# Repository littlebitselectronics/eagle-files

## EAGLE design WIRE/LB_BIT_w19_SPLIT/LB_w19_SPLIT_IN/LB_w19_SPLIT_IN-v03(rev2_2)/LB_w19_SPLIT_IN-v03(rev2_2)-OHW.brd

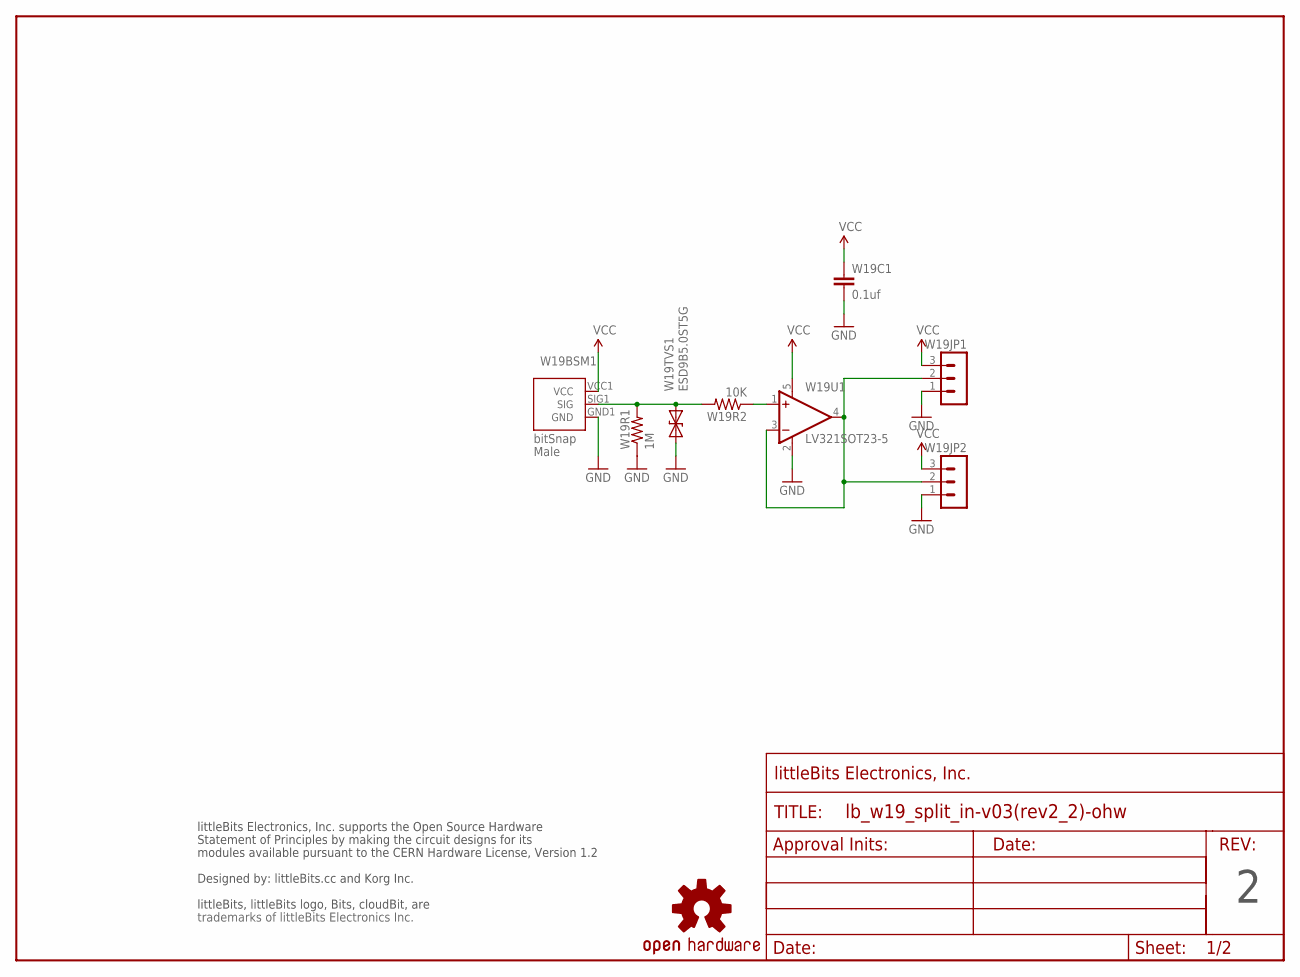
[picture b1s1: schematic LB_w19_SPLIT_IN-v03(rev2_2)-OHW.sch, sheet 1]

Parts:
FRAME1: FRAME-LETTER-OHWOHW; FABDWG01-OHW
U$3: OSHW-LOGOL; OSHW-LOGO-L
U$4: OSHWCREDIT-KORG
W19BSM1: BITSNAP_V03_MALE
W19C1: 0.1uf; CAP-0603
W19JP1, W19JP2: MA03-1SMD; 1X03-1MM-RA
W19R1: 1M; RES-0603
W19R2: 10K; RES-0603
W19TVS1: ESD9B5.0ST5G; SOD-923
W19U1: LV321SOT23-5; SOT23-5

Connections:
GND: W19BSM1.GND1 (GND), W19C1.2, W19JP1.1, W19JP2.1, W19R1.1, W19TVS1.1 (A), W19U1.2 (V-)
unnamed: W19BSM1.SIG1 (SIG), W19R1.2, W19R2.2, W19TVS1.2 (C)
unnamed: W19R2.1, W19U1.1 (+IN)
unnamed: W19JP1.2, W19JP2.2, W19U1.3 (-IN), W19U1.4 (OUT)
VCC: W19BSM1.VCC1 (VCC), W19C1.1, W19JP1.3, W19JP2.3, W19U1.5 (V+)

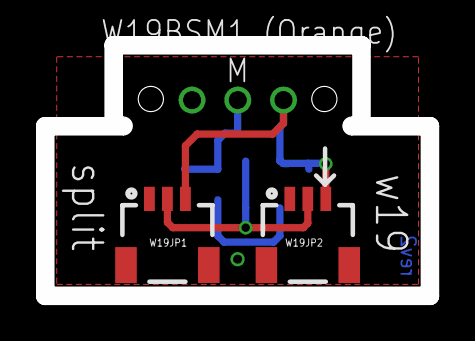
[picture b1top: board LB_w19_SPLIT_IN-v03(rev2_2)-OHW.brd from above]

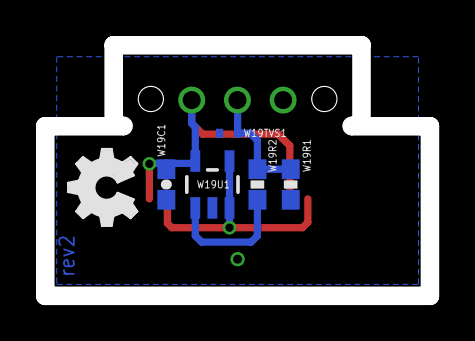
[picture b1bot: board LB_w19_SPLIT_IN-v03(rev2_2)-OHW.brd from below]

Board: 2 copper layers, 21.4 x 13.9 mm, 12 parts (5 on the bottom side), 5 nets.

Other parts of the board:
U$2: OSHW_FILLX150_NOTEXT

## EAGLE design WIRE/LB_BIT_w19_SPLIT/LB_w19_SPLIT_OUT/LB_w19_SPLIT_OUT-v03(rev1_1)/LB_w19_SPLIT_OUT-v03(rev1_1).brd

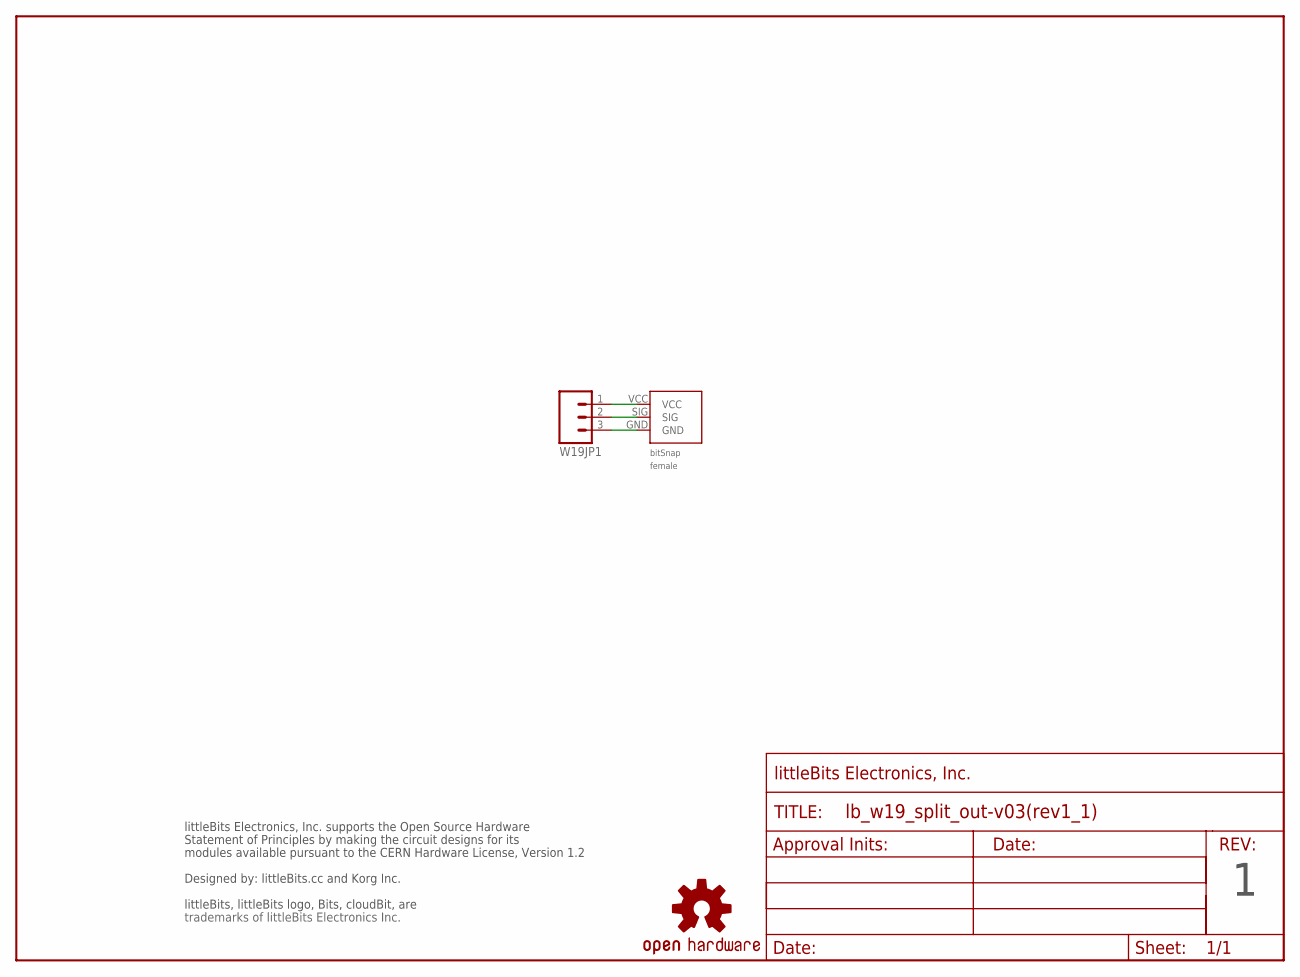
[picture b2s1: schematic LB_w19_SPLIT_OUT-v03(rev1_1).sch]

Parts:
FRAME1: FRAME-LETTER-OHWOHW; FABDWG01-OHW
U$3: OSHW-LOGOL; OSHW-LOGO-L
U$4: OSHWCREDIT-KORG
W19BSF1: BITSNAP_V03_FEMALE
W19JP1: M03SMD; 1X03-1MM-RA

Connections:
GND: W19BSF1.GND, W19JP1.3
SIG: W19BSF1.SIG, W19JP1.2
VCC: W19BSF1.VCC, W19JP1.1

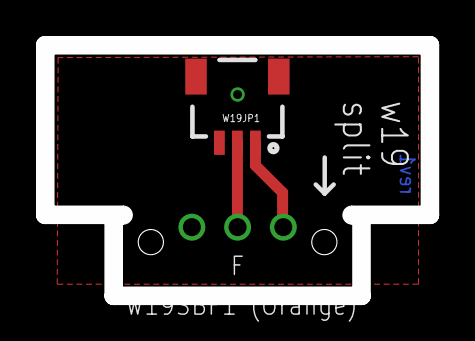
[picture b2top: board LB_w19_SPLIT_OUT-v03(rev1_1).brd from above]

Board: 2 copper layers, 21.4 x 13.9 mm, 6 parts (0 on the bottom side), 3 nets.

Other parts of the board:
U$2: OSHW_FILLX150_NOTEXT

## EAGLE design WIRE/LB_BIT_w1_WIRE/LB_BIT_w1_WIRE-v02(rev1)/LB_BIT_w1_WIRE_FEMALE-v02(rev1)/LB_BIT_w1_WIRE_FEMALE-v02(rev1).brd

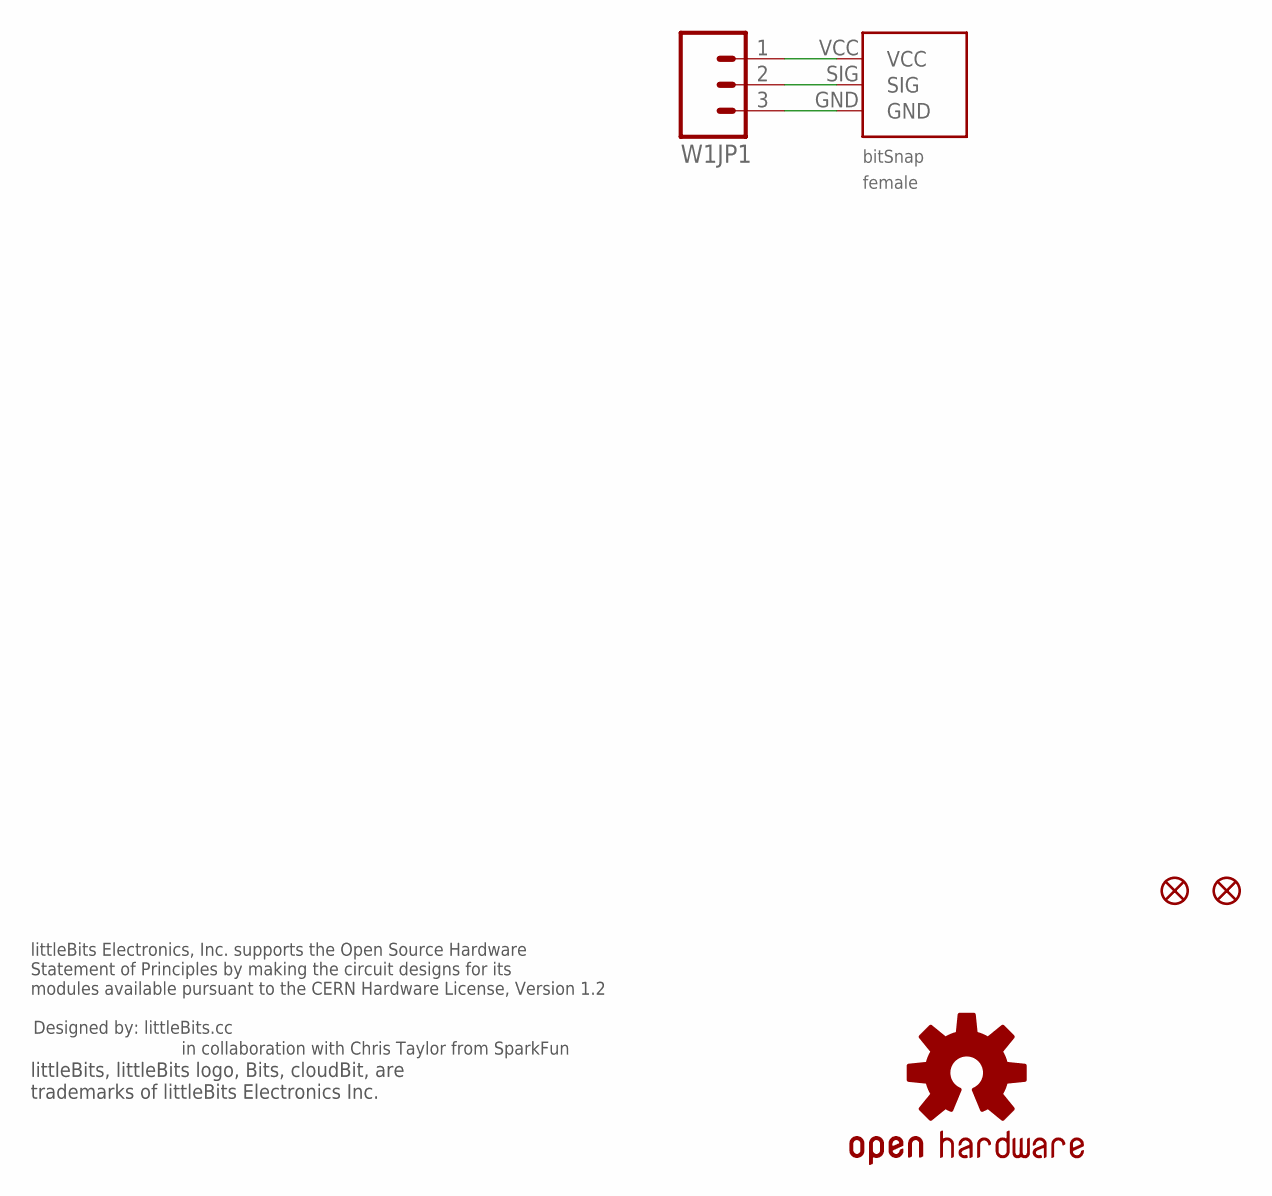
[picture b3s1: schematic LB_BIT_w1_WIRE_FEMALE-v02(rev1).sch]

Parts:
JP2, JP3: FIDUCIAL1X2.5; FIDUCIAL-1X2.5
U$1: LB_CREDITS; OSHWCREDIT
U$3: OSHW-LOGOL; OSHW-LOGO-L
W1BSF: BITSNAP_FEMALE
W1JP1: M03SMD; 1X03-1MM-RA

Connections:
GND: W1BSF.GND, W1JP1.3
SIG: W1BSF.SIG, W1JP1.2
VCC: W1BSF.VCC, W1JP1.1

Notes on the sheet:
in collaboration with Chris Taylor from SparkFun

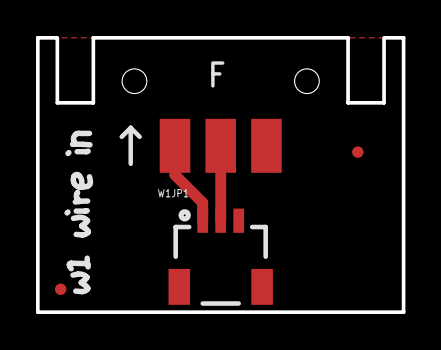
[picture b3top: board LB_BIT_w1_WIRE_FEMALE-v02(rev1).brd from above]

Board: 2 copper layers, 20.3 x 15.2 mm, 7 parts (0 on the bottom side), 3 nets.

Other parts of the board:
U$2: OSHW_FILLX150_NOTEXT

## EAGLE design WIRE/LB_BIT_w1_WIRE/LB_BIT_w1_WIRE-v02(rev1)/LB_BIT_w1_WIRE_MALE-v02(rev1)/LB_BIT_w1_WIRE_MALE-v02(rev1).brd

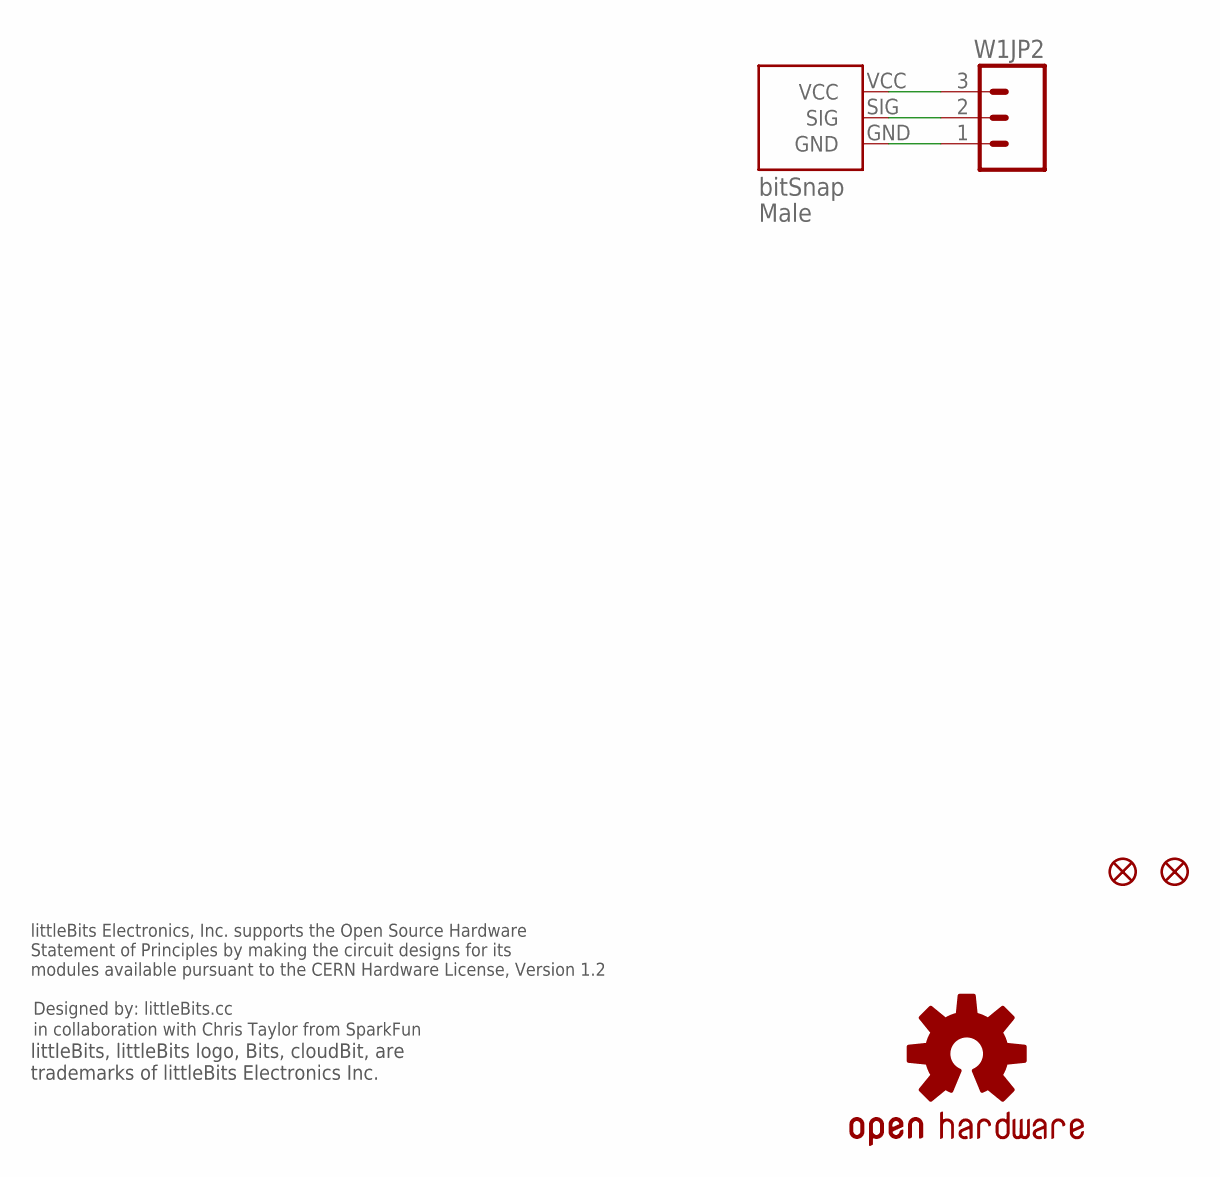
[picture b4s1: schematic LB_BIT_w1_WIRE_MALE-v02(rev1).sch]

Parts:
JP1, JP2: FIDUCIAL1X2.5; FIDUCIAL-1X2.5
U$1: OSHWCREDIT
U$3: OSHW-LOGOL; OSHW-LOGO-L
W1BSM: BITSNAP_MALE
W1JP2: M03SMD; 1X03-1MM-RA

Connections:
GND: W1BSM.GND, W1JP2.1
SIG: W1BSM.SIG, W1JP2.2
VCC: W1BSM.VCC, W1JP2.3

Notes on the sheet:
in collaboration with Chris Taylor from SparkFun

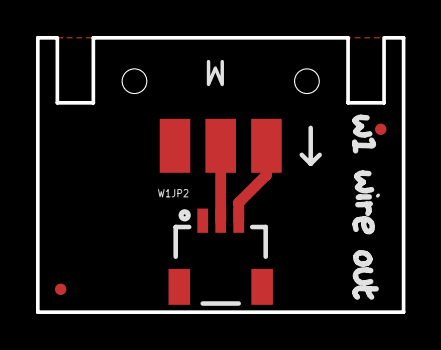
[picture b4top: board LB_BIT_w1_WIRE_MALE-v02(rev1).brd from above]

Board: 2 copper layers, 20.3 x 15.2 mm, 7 parts (0 on the bottom side), 3 nets.

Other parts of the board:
U$4: OSHW_FILLX150_NOTEXT

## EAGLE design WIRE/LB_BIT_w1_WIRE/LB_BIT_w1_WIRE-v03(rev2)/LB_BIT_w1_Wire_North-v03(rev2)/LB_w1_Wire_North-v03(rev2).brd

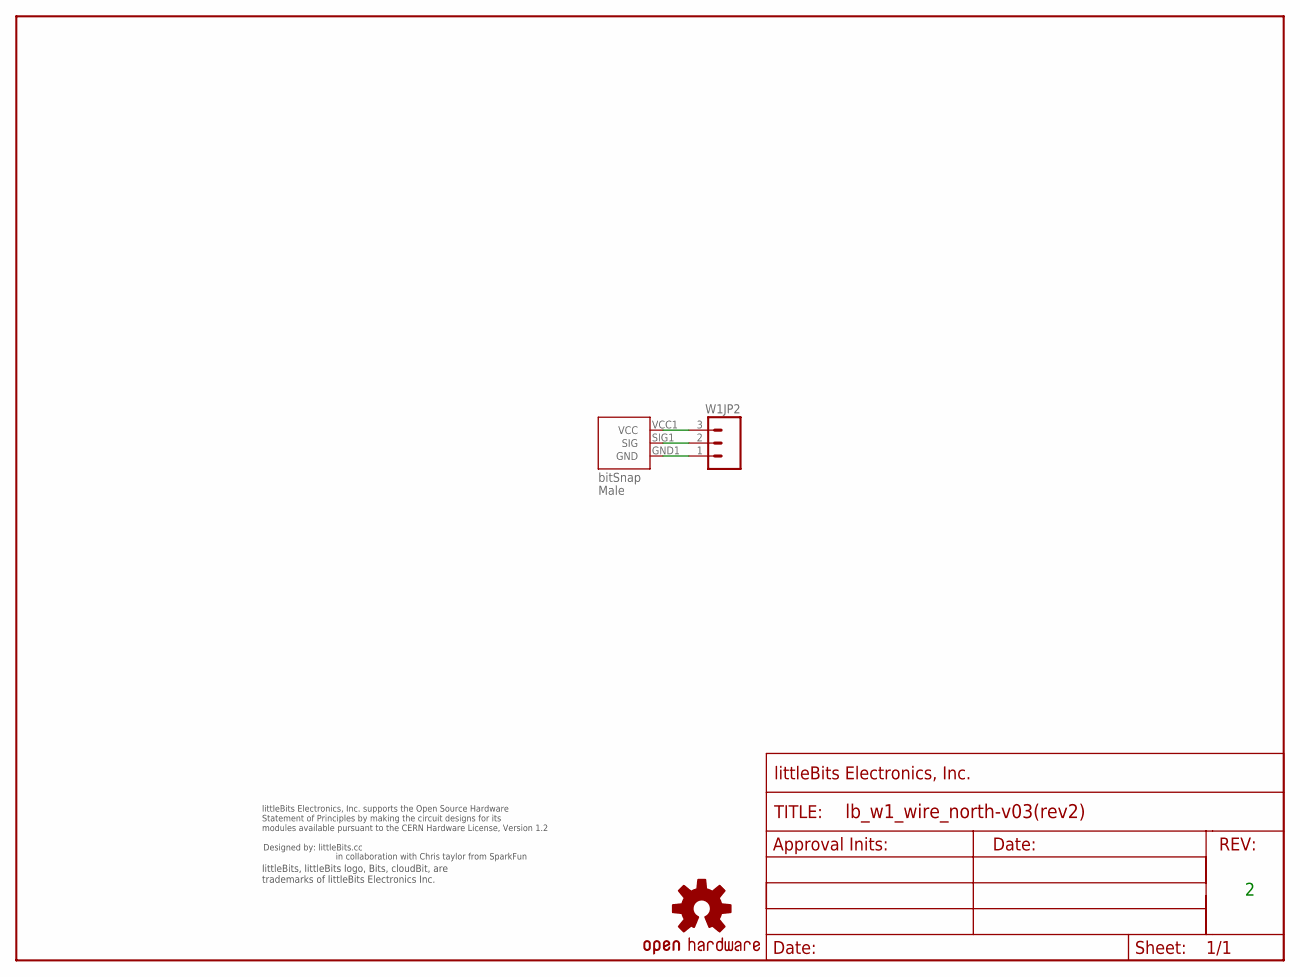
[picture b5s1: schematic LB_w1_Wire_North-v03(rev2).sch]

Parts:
FRAME1: FRAME-LETTER-OHWOHW; FABDWG01-OHW
U$1: OSHWCREDIT
U$3: OSHW-LOGOL; OSHW-LOGO-L
W1BSM1: BITSNAP_V03_MALE
W1JP2: M03SMD; 1X03-1MM-RA

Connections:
GND: W1BSM1.GND1 (GND), W1JP2.1
SIG: W1BSM1.SIG1 (SIG), W1JP2.2
VCC: W1BSM1.VCC1 (VCC), W1JP2.3

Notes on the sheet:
in collaboration with Chris taylor from SparkFun

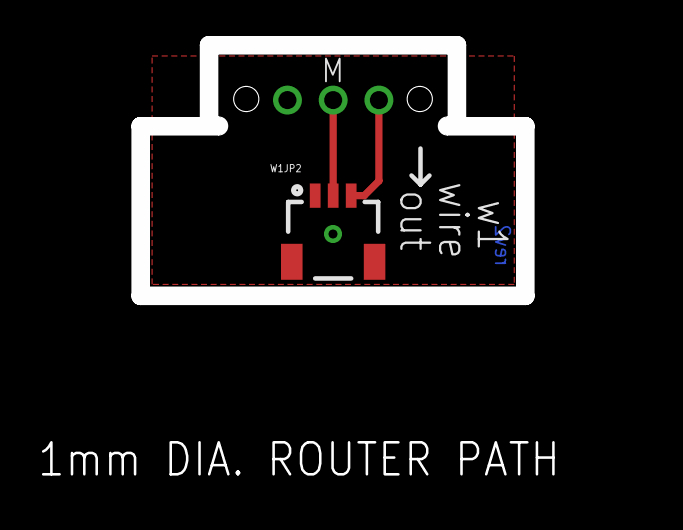
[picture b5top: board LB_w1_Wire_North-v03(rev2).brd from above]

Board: 2 copper layers, 21.4 x 13.9 mm, 6 parts (0 on the bottom side), 3 nets.

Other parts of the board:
U$4: OSHW_FILLX150_NOTEXT

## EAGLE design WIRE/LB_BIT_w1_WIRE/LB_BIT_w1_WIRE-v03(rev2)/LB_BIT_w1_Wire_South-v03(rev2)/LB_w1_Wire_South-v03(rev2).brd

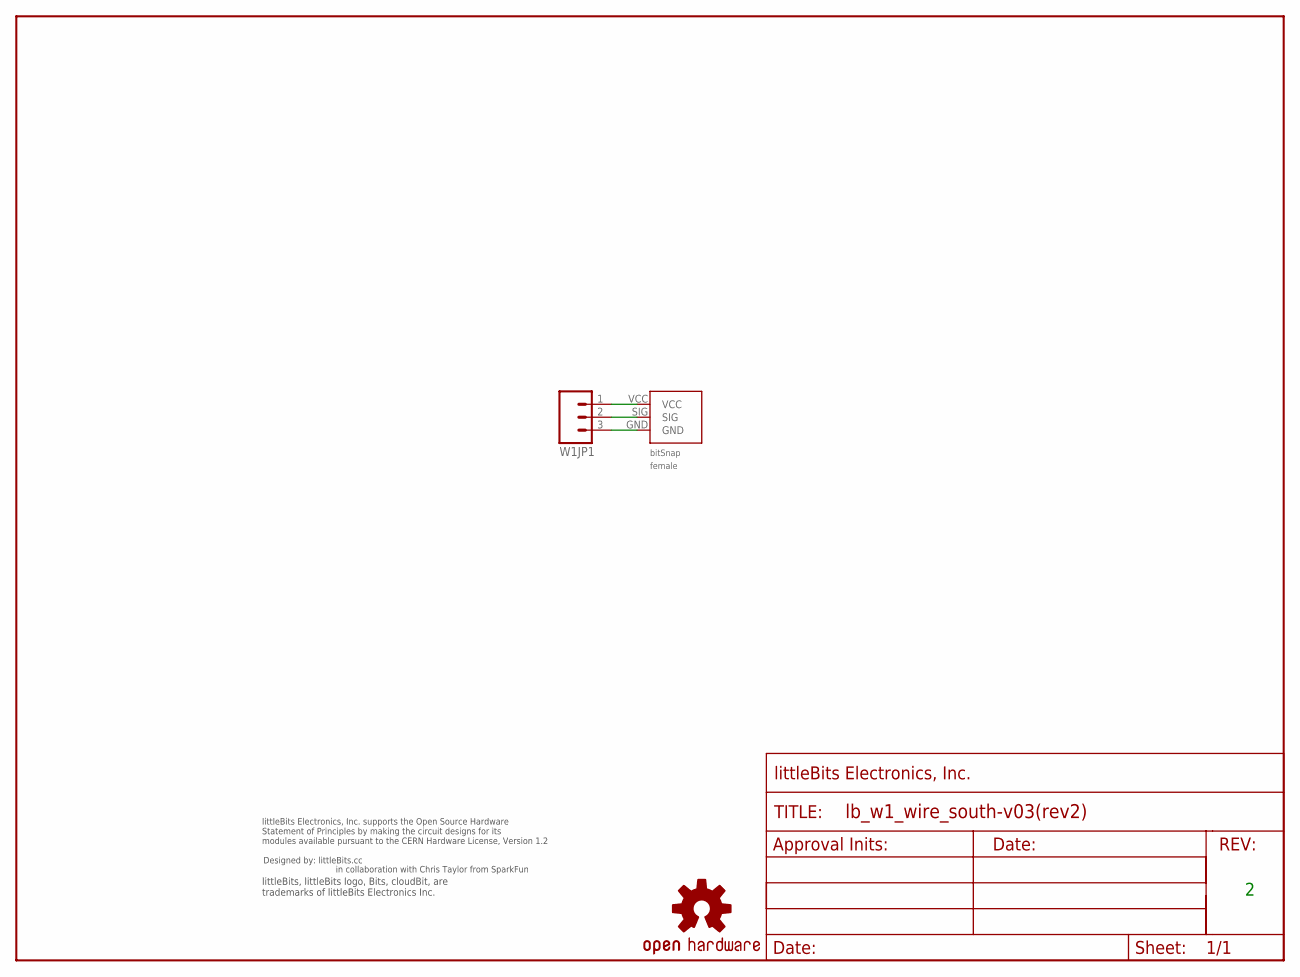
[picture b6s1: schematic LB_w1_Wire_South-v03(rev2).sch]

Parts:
FRAME1: FRAME-LETTER-OHWOHW; FABDWG01-OHW
U$1: OSHWCREDIT
U$3: OSHW-LOGOL; OSHW-LOGO-L
W1BSF1: BITSNAP_V03_FEMALE
W1JP1: M03SMD; 1X03-1MM-RA

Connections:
GND: W1BSF1.GND, W1JP1.3
SIG: W1BSF1.SIG, W1JP1.2
VCC: W1BSF1.VCC, W1JP1.1

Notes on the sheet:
in collaboration with Chris Taylor from SparkFun

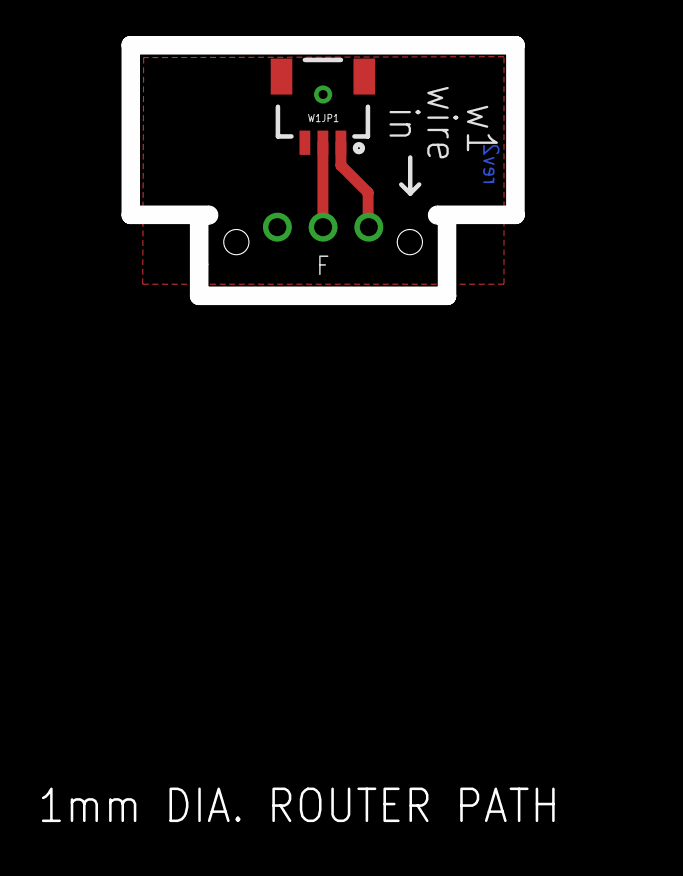
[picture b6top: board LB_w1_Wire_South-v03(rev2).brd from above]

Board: 2 copper layers, 21.4 x 13.9 mm, 6 parts (0 on the bottom side), 3 nets.

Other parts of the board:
U$2: OSHW_FILLX150_NOTEXT

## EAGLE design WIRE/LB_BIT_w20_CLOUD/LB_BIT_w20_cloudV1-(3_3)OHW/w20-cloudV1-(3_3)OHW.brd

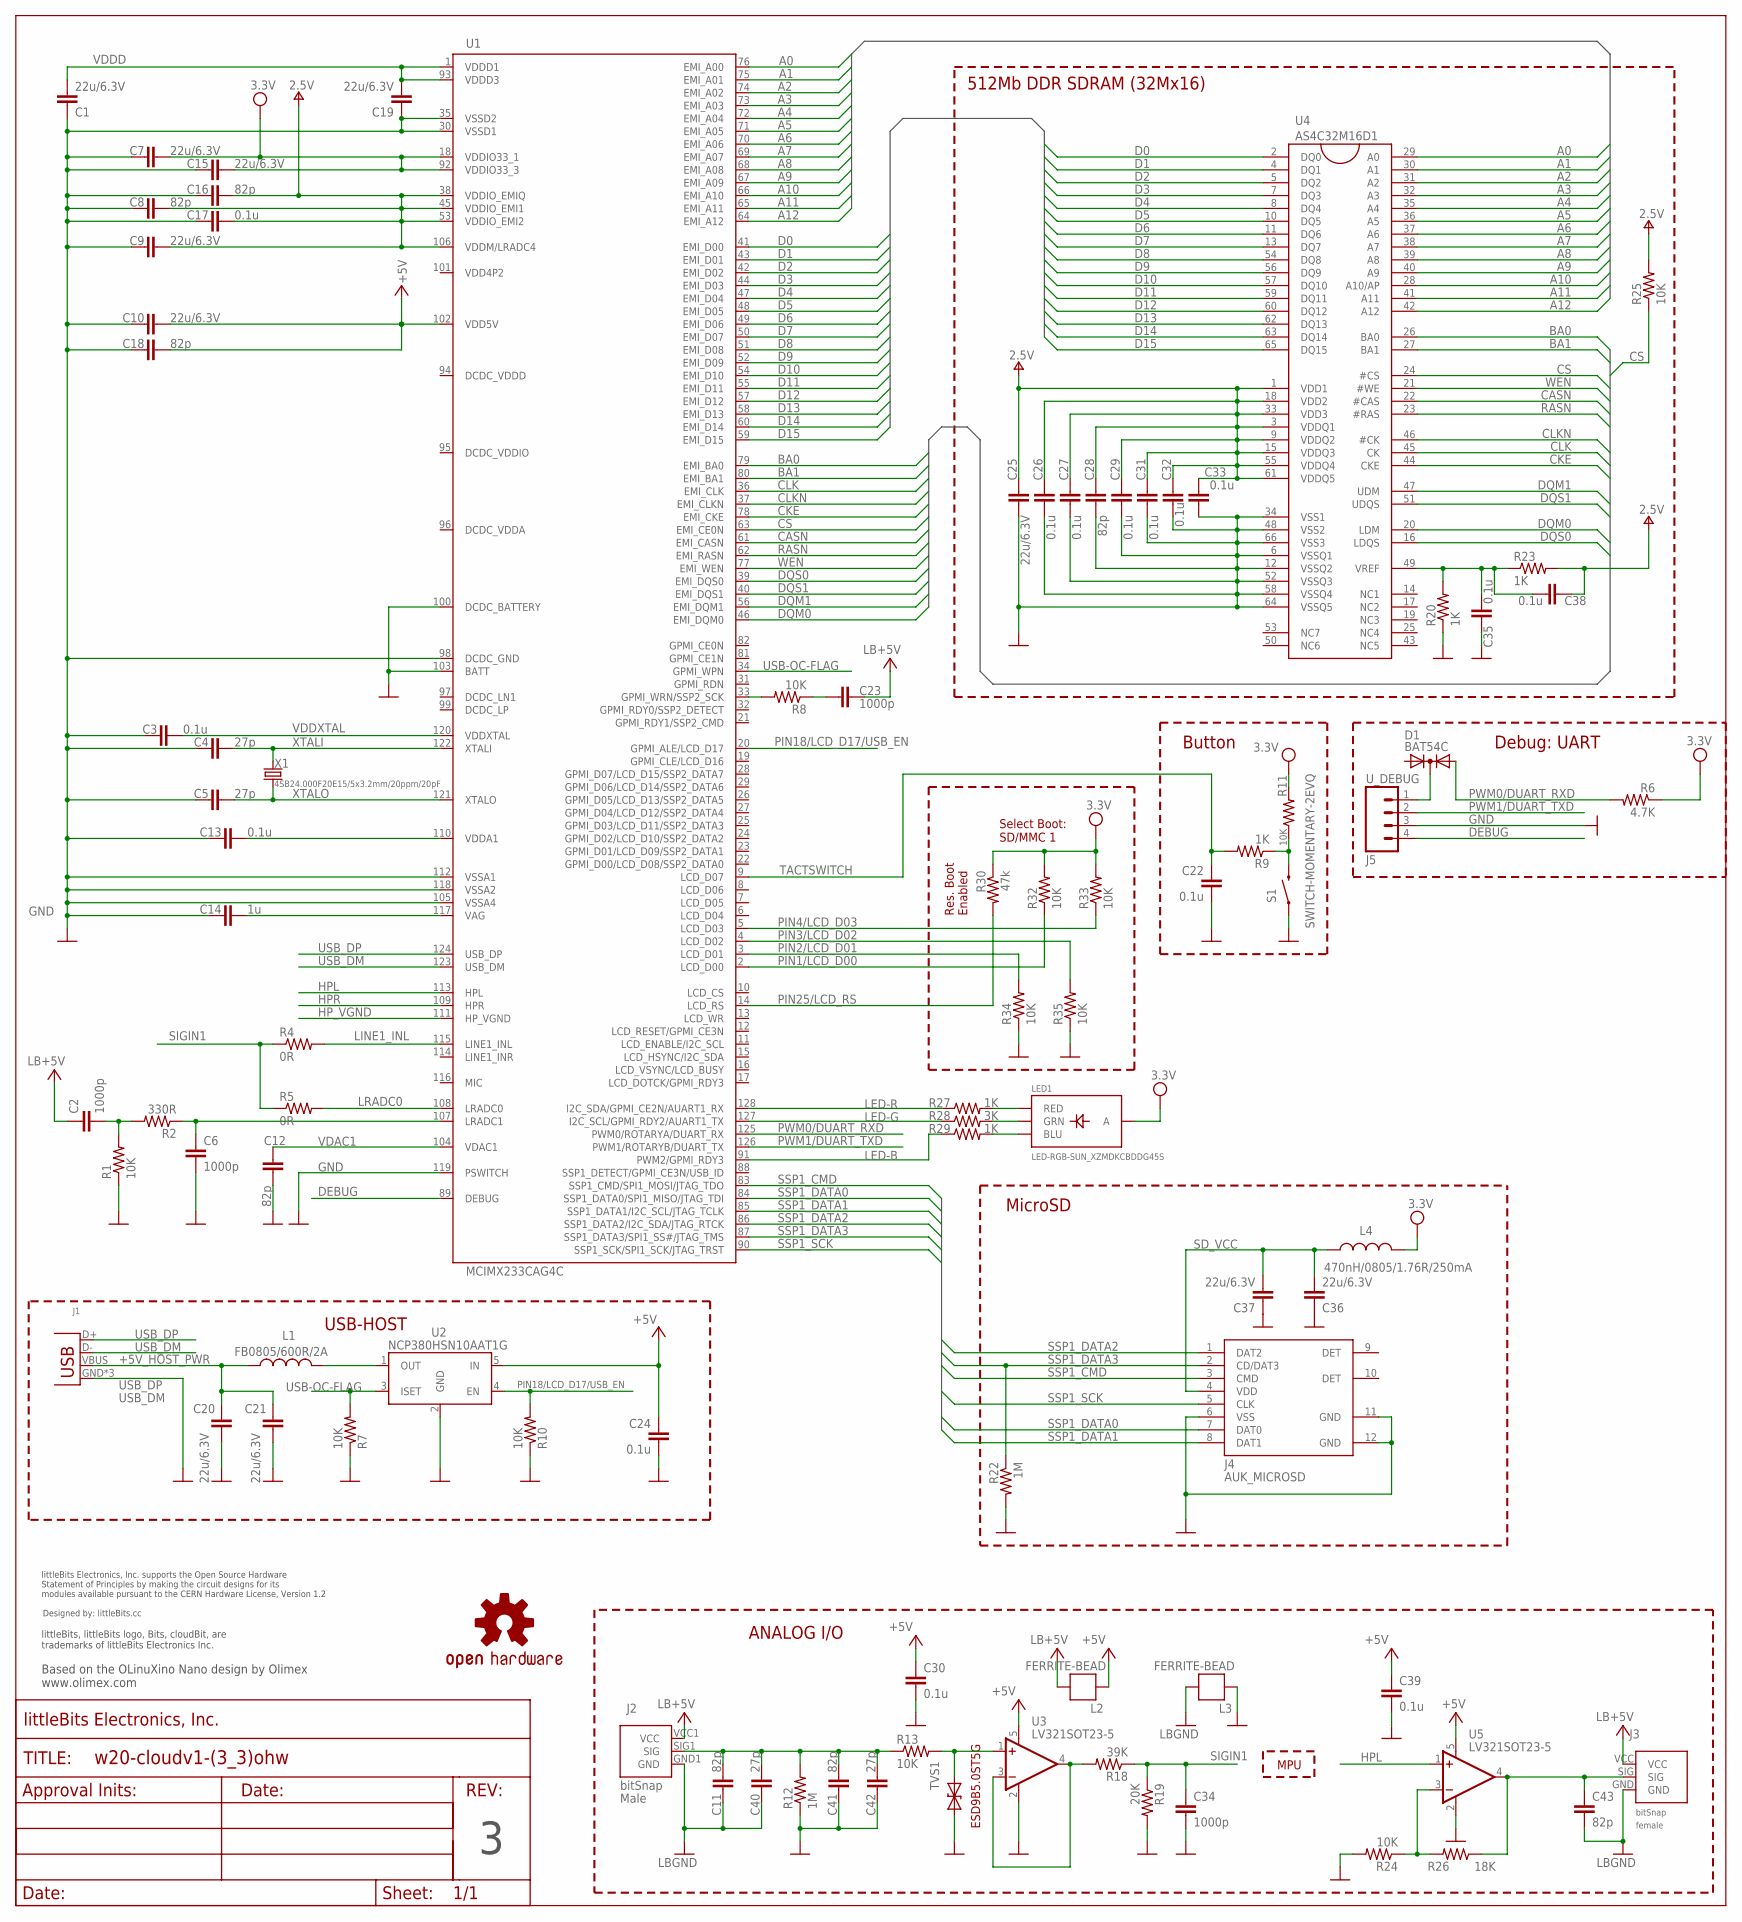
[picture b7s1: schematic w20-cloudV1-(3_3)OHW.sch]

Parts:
C1, C7, C9, C10, C15, C19, C20, C21, C25, C36, C37: 22u/6.3V; CAP-0603
C2, C23: 1000p; CAP-0603
C3, C13, C17, C22, C24, C26, C27, C29, C30, C31, C32, C33, C35, C38, C39: 0.1u; CAP-0402
C4, C5, C40, C42: 27p; CAP-0402
C6, C34: 1000p; CAP-0402
C8, C11, C12, C16, C18, C28, C41, C43: 82p; CAP-0402
C14: 1u; CAP-0402
D1: BAT54C; SOT23C
J1: USBFEMALE; USB-A-H-FEMALE
J2: BITSNAP_V03_MALE
J3: BITSNAP_V03_FEMALE
J4: AUK_MICROSD; AUK_TFC08WP01-R1K-H
J5: U_DEBUG; SIP4-SM-0.1IN-NOS.S.
L1: FB0805/600R/2A; L0805_5MIL_DWS
L2, L3: FERRITE-BEAD; R0603
L4: 470nH/0805/1.76R/250mA; L0805_5MIL_DWS
LED1: LED-RGB-SUN_XZMDKCBDDG45S
R1, R7, R8, R10, R11, R13, R24, R25, R32, R33, R34, R35: 10K; RES-0603
R2: 330R; RES-0603
R4, R5: 0R; RES-0603
R6: 4.7K; RES-0603
R9, R20, R23, R27, R29: 1K; RES-0603
R12, R22: 1M; RES-0603
R18: 39K; RES-0603
R19: 20K; RES-0603
R26: 18K; RES-0603
R28: 3K; RES-0603
R30: 47k; RES-0603
S1: SWITCH-MOMENTARY-2EVQ; TACTILE-SWITCH-EVQ-PE104K
TVS1: DIODE-TVSSOD-923; SOD-923
U1: MCIMX233CAG4C; TQFP128LD
U2: NCP380HSN10AAT1G; SOT23-5
U3, U5: LV321SOT23-5; SOT23-5
U4: AS4C32M16D1; 66TSOP-II
U$2: OSHWCREDIT
U$4: OSHW-LOGOL; OSHW-LOGO-L
U$5: FRAME-LETTER-OHWOHW; FABDWG01-OHW
X1: 4SB24.000F20E15/5x3.2mm/20ppm/20pF; HCX-4S

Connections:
+5V: C10.2, C18.2, C24.1, C30.1, C39.1, L2.2, U1.102 (VDD5V), U2.5 (IN), U3.5 (V+), U5.5 (V+)
+5V_HOST_PWR: C20.1, C21.1, J1.VBUS, L1.1
A0: U1.76 (EMI_A00), U4.29 (A0)
A1: U1.75 (EMI_A01), U4.30 (A1)
A2: U1.74 (EMI_A02), U4.31 (A2)
A3: U1.73 (EMI_A03), U4.32 (A3)
A4: U1.72 (EMI_A04), U4.35 (A4)
A5: U1.71 (EMI_A05), U4.36 (A5)
A6: U1.70 (EMI_A06), U4.37 (A6)
A7: U1.69 (EMI_A07), U4.38 (A7)
A8: U1.68 (EMI_A08), U4.39 (A8)
A9: U1.67 (EMI_A09), U4.40 (A9)
A10: U1.66 (EMI_A10), U4.28 (A10/AP)
A11: U1.65 (EMI_A11), U4.41 (A11)
A12: U1.64 (EMI_A12), U4.42 (A12)
BA0: U1.79 (EMI_BA0), U4.26 (BA0)
BA1: U1.80 (EMI_BA1), U4.27 (BA1)
CASN: U1.61 (EMI_CASN), U4.22 (#CAS)
CKE: U1.78 (EMI_CKE), U4.44 (CKE)
CLK: U1.36 (EMI_CLK), U4.45 (CK)
CLKN: U1.37 (EMI_CLKN), U4.46 (#CK)
CS: R25.1, U1.63 (EMI_CE0N), U4.24 (#CS)
D0: U1.41 (EMI_D00), U4.2 (DQ0)
D1: U1.43 (EMI_D01), U4.4 (DQ1)
D2: U1.42 (EMI_D02), U4.5 (DQ2)
D3: U1.44 (EMI_D03), U4.7 (DQ3)
D4: U1.47 (EMI_D04), U4.8 (DQ4)
D5: U1.48 (EMI_D05), U4.10 (DQ5)
D6: U1.49 (EMI_D06), U4.11 (DQ6)
D7: U1.50 (EMI_D07), U4.13 (DQ7)
D8: U1.51 (EMI_D08), U4.54 (DQ8)
D9: U1.52 (EMI_D09), U4.56 (DQ9)
D10: U1.54 (EMI_D10), U4.57 (DQ10)
D11: U1.55 (EMI_D11), U4.59 (DQ11)
D12: U1.57 (EMI_D12), U4.60 (DQ12)
D13: U1.58 (EMI_D13), U4.62 (DQ13)
D14: U1.60 (EMI_D14), U4.63 (DQ14)
D15: U1.59 (EMI_D15), U4.65 (DQ15)
DEBUG: J5.4, U1.89 (DEBUG)
DQM0: U1.46 (EMI_DQM0), U4.20 (LDM)
DQM1: U1.56 (EMI_DQM1), U4.47 (UDM)
DQS0: U1.39 (EMI_DQS0), U4.16 (LDQS)
DQS1: U1.40 (EMI_DQS1), U4.51 (UDQS)
GND: C1.1, C3.1, C4.1, C5.1, C6.2, C7.1, C8.1, C9.1, C10.1, C12.2, C13.1, C14.1, C15.1, C16.1, C17.1, C18.1, C19.1, C20.2, C21.2, C22.2, C24.2, C25.1, C26.1, C27.1, C28.1, C29.1, C30.2, C31.1, C32.1, C33.1, C34.2, C35.1, C36.1, C37.1, C39.2, C41.2, C42.2, J1.GND, J1.GND@1 (GND), J1.GND@2 (GND), J4.6 (VSS), J4.11 (GND), J4.12 (GND), J5.3, L3.2, R1.1, R7.1, R10.1, R12.1, R19.2, R20.1, R22.2, R24.2, R34.1, R35.1, S1.P$1 (1), TVS1.1 (A), U1.30 (VSSD1), U1.35 (VSSD2), U1.98 (DCDC_GND), U1.100 (DCDC_BATTERY), U1.103 (BATT), U1.105 (VSSA4), U1.112 (VSSA1), U1.118 (VSSA2), U1.119 (PSWITCH), U2.2 (GND), U3.2 (V-), U4.6 (VSSQ1), U4.12 (VSSQ2), U4.34 (VSS1), U4.48 (VSS2), U4.52 (VSSQ3), U4.58 (VSSQ4), U4.64 (VSSQ5), U4.66 (VSS3), U5.2 (V-)
HPL: U1.113 (HPL), U5.1 (+IN)
HPR: U1.109 (HPR)
HP_VGND: U1.111 (HP_VGND)
LB+5V: C2.1, C23.2, J2.VCC1 (VCC), J3.VCC, L2.1
LBGND: C11.2, C40.2, C43.2, J2.GND1 (GND), J3.GND, L3.1
LED-B: R29.1, U1.91 (PWM2/GPMI_RDY3)
LED-G: R28.1, U1.127 (I2C_SCL/GPMI_RDY2/AUART1_TX)
LED-R: R27.1, U1.128 (I2C_SDA/GPMI_CE2N/AUART1_RX)
LINE1_INL: R4.2, U1.115 (LINE1_INL)
LRADC0: R5.2, U1.108 (LRADC0)
unnamed: R9.1, R11.1, S1.P$2 (2)
unnamed: LED1.1 (RED), R27.2
unnamed: L1.2, U2.1 (OUT)
unnamed: LED1.4 (GRN), R28.2
unnamed: LED1.3 (BLU), R29.2
unnamed: C35.2, C38.2, R20.2, R23.1, U4.49 (VREF)
unnamed: R18.2, U3.3 (-IN), U3.4 (OUT)
unnamed: R13.2, TVS1.2 (C), U3.1 (+IN)
unnamed: D1.3 (K), J5.1
unnamed: R24.1, R26.2, U5.3 (-IN)
unnamed: C11.1, C40.1, C41.1, C42.1, J2.SIG1 (SIG), R12.2, R13.1
unnamed: C43.1, J3.SIG, R26.1, U5.4 (OUT)
unnamed: C13.2, U1.110 (VDDA1)
unnamed: R8.2, U1.33 (GPMI_WRN/SSP2_SCK)
unnamed: C23.1, R8.1
unnamed: C6.1, R2.1, U1.107 (LRADC1)
unnamed: C2.2, R1.2, R2.2
unnamed: C14.2, U1.117 (VAG)
PIN1/LCD_D00: R32.1, U1.2 (LCD_D00)
PIN2/LCD_D01: R34.2, U1.3 (LCD_D01)
PIN3/LCD_D02: R35.2, U1.4 (LCD_D02)
PIN4/LCD_D03: R33.1, U1.5 (LCD_D03)
PIN18/LCD_D17/USB_EN: R10.2, U1.20 (GPMI_ALE/LCD_D17), U2.4 (EN)
PIN25/LCD_RS: R30.2, U1.14 (LCD_RS)
PWM0/DUART_RXD: D1.2 (A2), R6.2, U1.125 (PWM0/ROTARYA/DUART_RX)
PWM1/DUART_TXD: J5.2, U1.126 (PWM1/ROTARYB/DUART_TX)
RASN: U1.62 (EMI_RASN), U4.23 (#RAS)
SD_VCC: C36.2, C37.2, J4.4 (VDD), L4.2
SIGIN1: C34.1, R4.1, R5.1, R18.1, R19.1
SSP1_CMD: J4.3 (CMD), U1.83 (SSP1_CMD/SPI1_MOSI/JTAG_TDO)
SSP1_DATA0: J4.7 (DAT0), U1.84 (SSP1_DATA0/SPI1_MISO/JTAG_TDI)
SSP1_DATA1: J4.8 (DAT1), U1.85 (SSP1_DATA1/I2C_SCL/JTAG_TCLK)
SSP1_DATA2: J4.1 (DAT2), U1.86 (SSP1_DATA2/I2C_SDA/JTAG_RTCK)
SSP1_DATA3: J4.2 (CD/DAT3), R22.1, U1.87 (SSP1_DATA3/SPI1_SS#/JTAG_TMS)
SSP1_SCK: J4.5 (CLK), U1.90 (SSP1_SCK/SPI1_SCK/JTAG_TRST)
TACTSWITCH: C22.1, R9.2, U1.9 (LCD_D07)
USB-OC-FLAG: R7.2, U1.34 (GPMI_WPN), U2.3 (ISET)
USB_DM: J1.D-, U1.123 (USB_DM)
USB_DP: J1.D+, U1.124 (USB_DP)
V+: C8.2, C9.2, C16.2, C17.2, C25.2, C26.2, C27.2, C28.2, C29.2, C31.2, C32.2, C33.2, C38.1, R23.2, R25.2, U1.38 (VDDIO_EMIQ), U1.45 (VDDIO_EMI1), U1.53 (VDDIO_EMI2), U1.106 (VDDM/LRADC4), U4.1 (VDD1), U4.3 (VDDQ1), U4.9 (VDDQ2), U4.15 (VDDQ3), U4.18 (VDD2), U4.33 (VDD3), U4.55 (VDDQ4), U4.61 (VDDQ5)
VCC: C7.2, C15.2, L4.1, LED1.2 (A), R6.1, R11.2, R30.1, R32.2, R33.2, U1.18 (VDDIO33_1), U1.92 (VDDIO33_3)
VDAC1: C12.1, U1.104 (VDAC1)
VDDD: C1.2, C19.2, U1.1 (VDDD1), U1.93 (VDDD3)
VDDXTAL: C3.2, U1.120 (VDDXTAL)
WEN: U1.77 (EMI_WEN), U4.21 (#WE)
XTALI: C4.2, U1.122 (XTALI), X1.2
XTALO: C5.2, U1.121 (XTALO), X1.1

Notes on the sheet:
512Mb DDR SDRAM (32Mx16)
MicroSD
Button
Res. Boot Enabled
Debug: UART
USB-HOST
MPU
Select Boot: SD/MMC 1
ANALOG I/O
Based on the OLinuXino Nano design by Olimex www.olimex.com

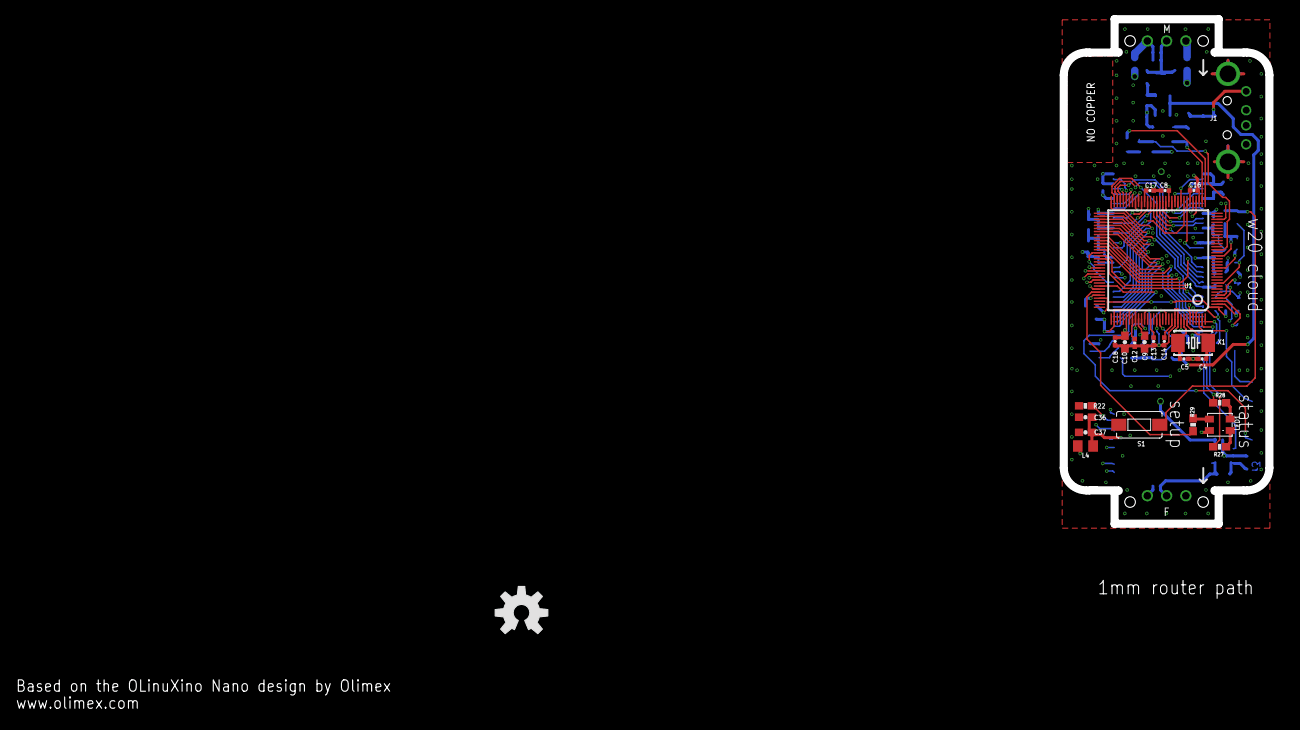
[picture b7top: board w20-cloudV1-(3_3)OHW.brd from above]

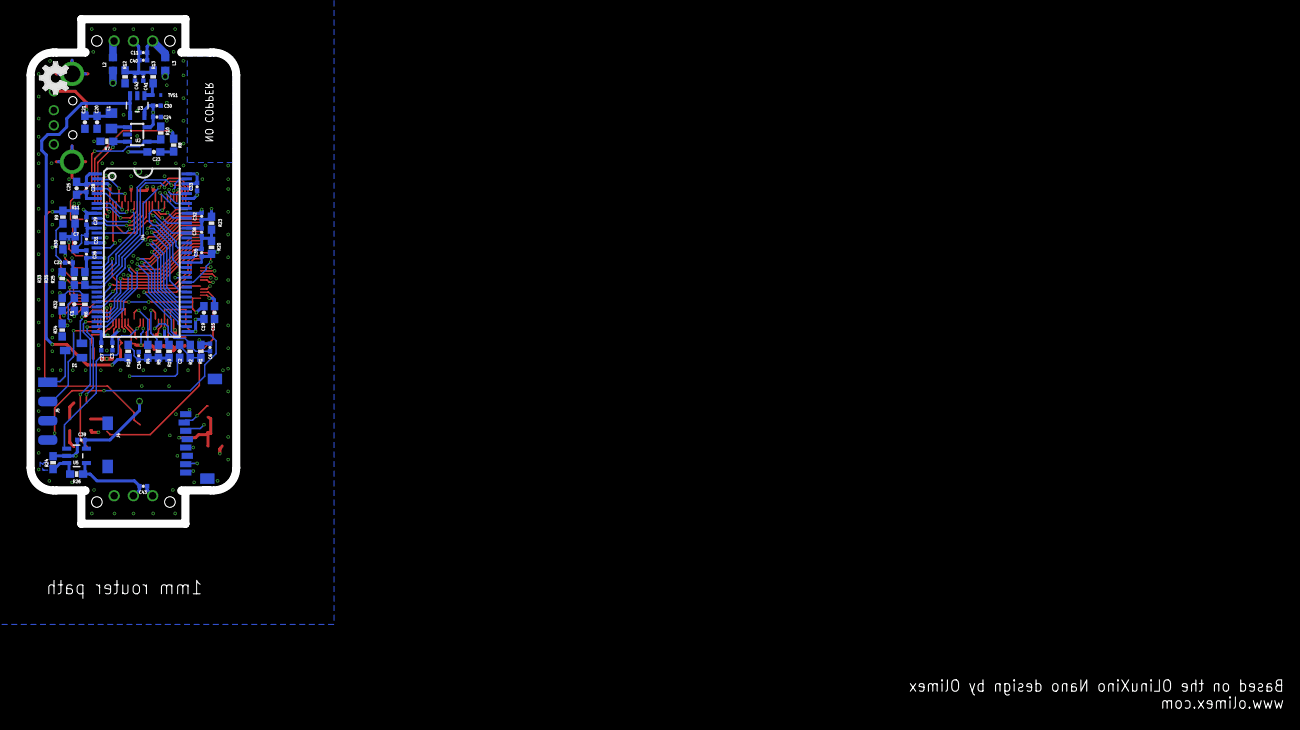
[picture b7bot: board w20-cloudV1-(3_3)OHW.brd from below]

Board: 6 copper layers, 27.2 x 66.6 mm, 95 parts (65 on the bottom side), 99 nets.

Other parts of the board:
DRILEGEND: DRILEGEND
U$1: OSHW_FILLX150_NOTEXT

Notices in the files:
parts and their libraries:
LITTLEBITS: modules available pursuant to the CERN Hardware License, Version 1.2
LITTLEBITS: modules available pursuant to the CERN Hardware License,
Version 1.2
LITTLEBITS: Released under the Creative Commons Attribution Share-Alike 3.0 License
